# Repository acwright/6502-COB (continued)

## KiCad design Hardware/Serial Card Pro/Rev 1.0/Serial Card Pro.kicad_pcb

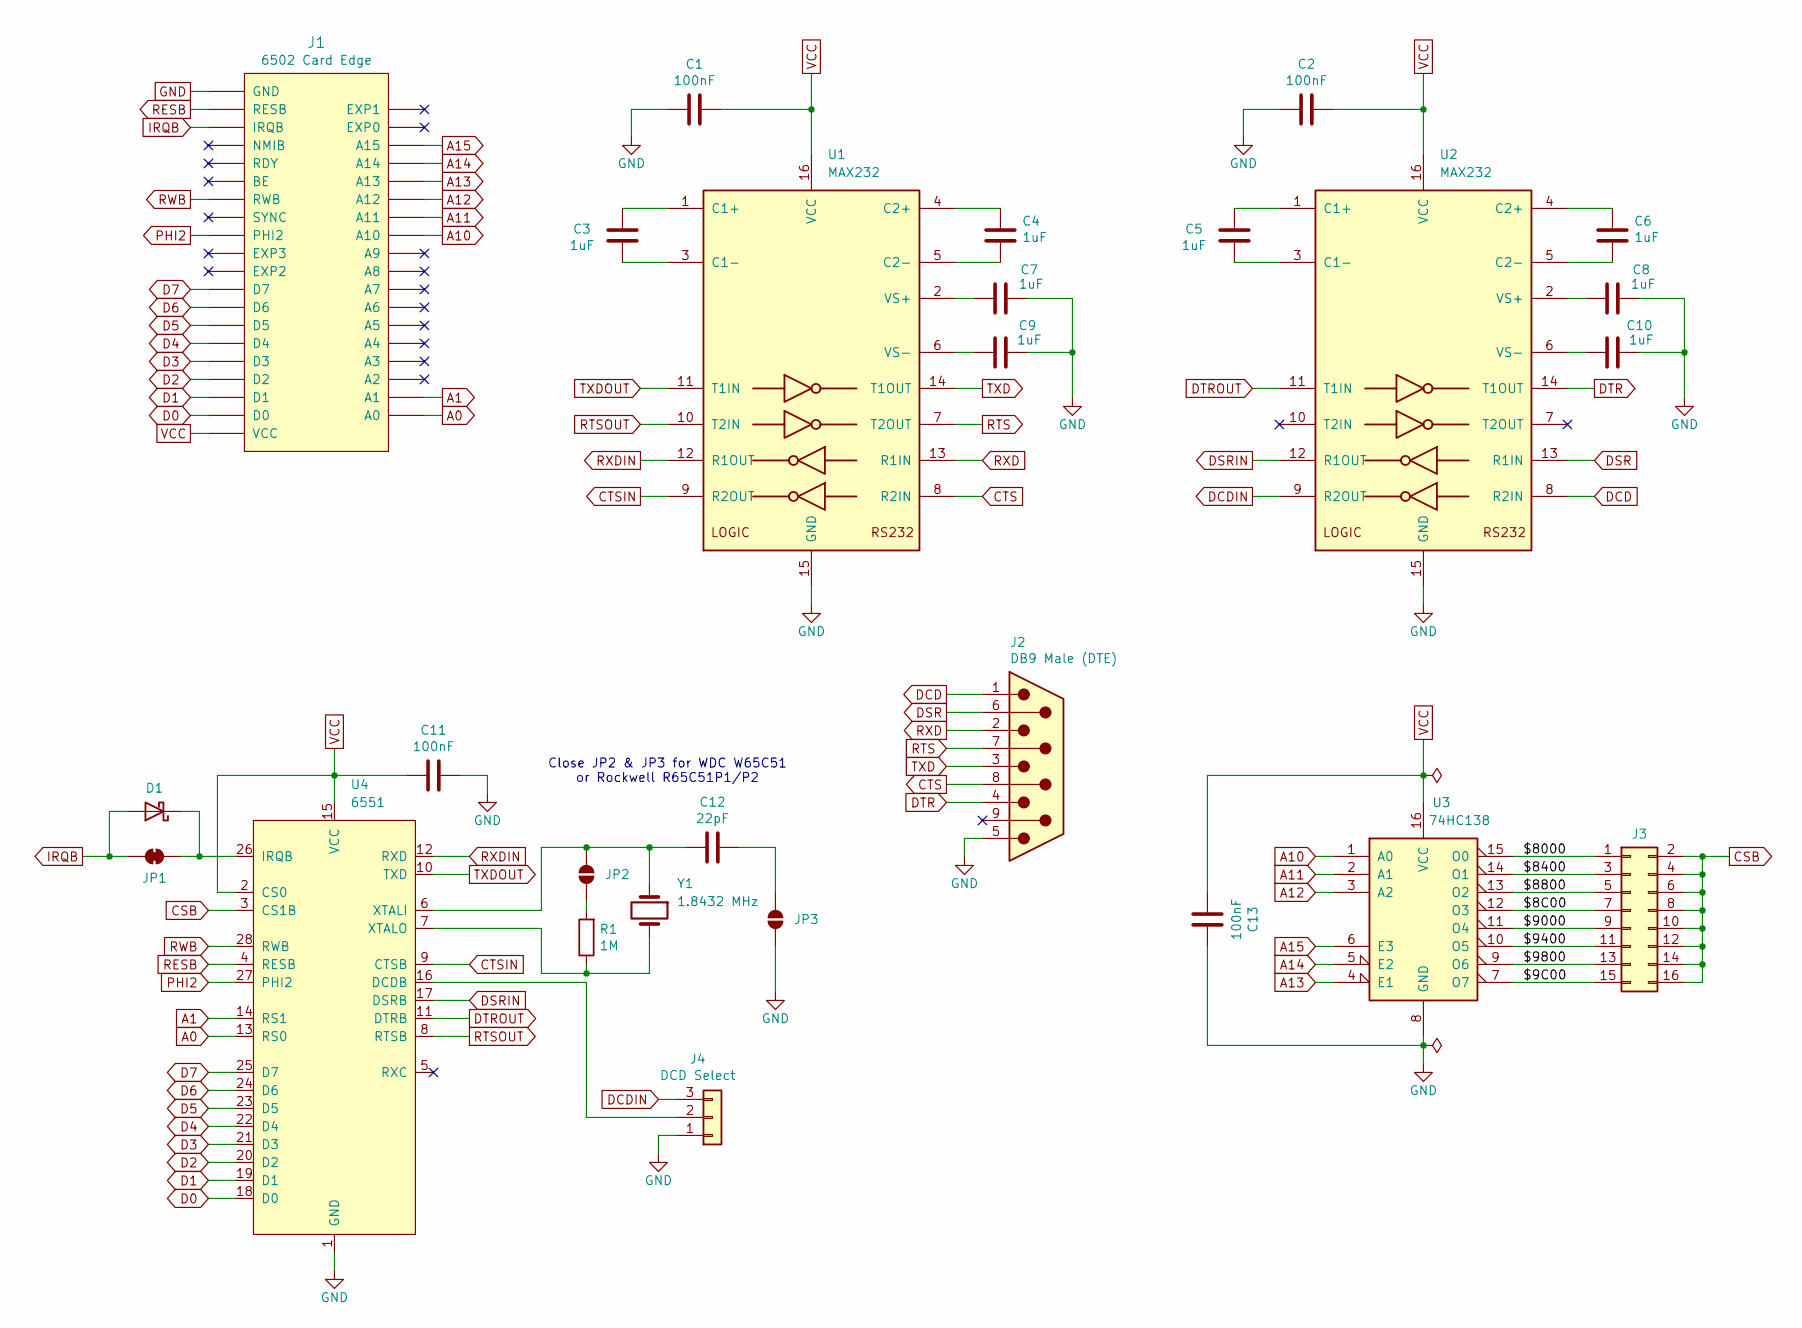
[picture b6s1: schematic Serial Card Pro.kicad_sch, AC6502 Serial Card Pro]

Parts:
C1, C2, C11, C13: 100nF; C_0805_2012Metric; LCSC C49678
C3, C4, C5, C6, C7, C8, C9, C10: 1uF; C_0805_2012Metric; LCSC C28323
C12: 22pF; C_0805_2012Metric; LCSC C1804
D1: BAT85; D_DO-35_SOD27_P7.62mm_Horizontal; Digikey BAT85SCT-ND
J1: 6502 Card Edge
J2: DB9 Male (DTE); DB9 Male; Digikey 609-1481-ND
J3: Conn_02x08_Odd_Even; PinHeader_2x08_P2.54mm_Vertical; Digikey S2011EC-40-ND
J4: DCD Select; PinHeader_1x03_P2.54mm_Vertical; Digikey S1011EC-40-ND
JP1: SolderJumper_2_Bridged; SolderJumper-2_P1.3mm_Bridged_RoundedPad1.0x1.5mm
JP2, JP3: SolderJumper_2_Open; SolderJumper-2_P1.3mm_Open_RoundedPad1.0x1.5mm
R1: 1M; R_0805_2012Metric; LCSC C17514
U1, U2: MAX232; SOIC-16; LCSC C59824
U3: 74HC138; SOIC-16_3.9x9.9mm_P1.27mm; LCSC C5602
U4: 6551; DIP-28_W15.24mm_Socket_LongPads
Y1: 1.8432 MHz; Crystal_HC49-U_Vertical; Digikey 535-9009-ND

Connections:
/$8C00: J3.7, U3.12 (O3)
/$9C00: J3.15, U3.7 (O7)
/$8000: J3.1, U3.15 (O0)
/$8400: J3.3, U3.14 (O1)
/$8800: J3.5, U3.13 (O2)
/$9000: J3.9, U3.11 (O4)
/$9400: J3.11, U3.10 (O5)
/$9800: J3.13, U3.9 (O6)
A0: J1.A0, U4.13 (RS0)
A1: J1.A1, U4.14 (RS1)
A10: J1.A10, U3.1 (A0)
A11: J1.A11, U3.2 (A1)
A12: J1.A12, U3.3 (A2)
A13: J1.A13, U3.4 (E1)
A14: J1.A14, U3.5 (E2)
A15: J1.A15, U3.6 (E3)
CSB: J3.2, J3.4, J3.6, J3.8, J3.10, J3.12, J3.14, J3.16, U4.3 (CS1B)
CTS: J2.8, U1.8 (R2IN)
CTSIN: U1.9 (R2OUT), U4.9 (CTSB)
D0: J1.D0, U4.18 (D0)
D1: J1.D1, U4.19 (D1)
D2: J1.D2, U4.20 (D2)
D3: J1.D3, U4.21 (D3)
D4: J1.D4, U4.22 (D4)
D5: J1.D5, U4.23 (D5)
D6: J1.D6, U4.24 (D6)
D7: J1.D7, U4.25 (D7)
DCD: J2.1, U2.8 (R2IN)
DCDIN: J4.3, U2.9 (R2OUT)
DSR: J2.6, U2.13 (R1IN)
DSRIN: U2.12 (R1OUT), U4.17 (DSRB)
DTR: J2.4, U2.14 (T1OUT)
DTROUT: U2.11 (T1IN), U4.11 (DTRB)
GND: C1.1, C2.1, C7.2, C8.2, C9.2, C10.2, C11.2, C13.2, J1.GND, J2.5, J4.1, JP3.1 (A), U1.15 (GND), U2.15 (GND), U3.8 (GND), U4.1 (GND)
IRQB: D1.2 (A), J1.IRQB, JP1.1 (A)
unnamed: D1.1 (K), JP1.2 (B), U4.26 (IRQB)
unnamed: J4.2, U4.16 (DCDB)
unnamed: JP2.1 (A), R1.2
unnamed: C12.2, JP2.2 (B), U4.6 (XTALI), Y1.1
unnamed: C12.1, JP3.2 (B)
unnamed: C3.1, U1.1 (C1+)
unnamed: C3.2, U1.3 (C1-)
unnamed: C4.1, U1.4 (C2+)
unnamed: C4.2, U1.5 (C2-)
unnamed: C7.1, U1.2 (VS+)
unnamed: C9.1, U1.6 (VS-)
unnamed: C5.1, U2.1 (C1+)
unnamed: C5.2, U2.3 (C1-)
unnamed: C6.1, U2.4 (C2+)
unnamed: C6.2, U2.5 (C2-)
unnamed: C8.1, U2.2 (VS+)
unnamed: C10.1, U2.6 (VS-)
unnamed: R1.1, U4.7 (XTALO), Y1.2
PHI2: J1.PHI2, U4.27 (PHI2)
RESB: J1.RESB, U4.4 (RESB)
RTS: J2.7, U1.7 (T2OUT)
RTSOUT: U1.10 (T2IN), U4.8 (RTSB)
RWB: J1.RWB, U4.28 (RWB)
RXD: J2.2, U1.13 (R1IN)
RXDIN: U1.12 (R1OUT), U4.12 (RXD)
TXD: J2.3, U1.14 (T1OUT)
TXDOUT: U1.11 (T1IN), U4.10 (TXD)
VCC: C1.2, C2.2, C11.1, C13.1, J1.VCC, U1.16 (VCC), U2.16 (VCC), U3.16 (VCC), U4.2 (CS0), U4.15 (VCC)

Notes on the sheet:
Close JP2 & JP3 for WDC W65C51 or Rockwell R65C51P1/P2

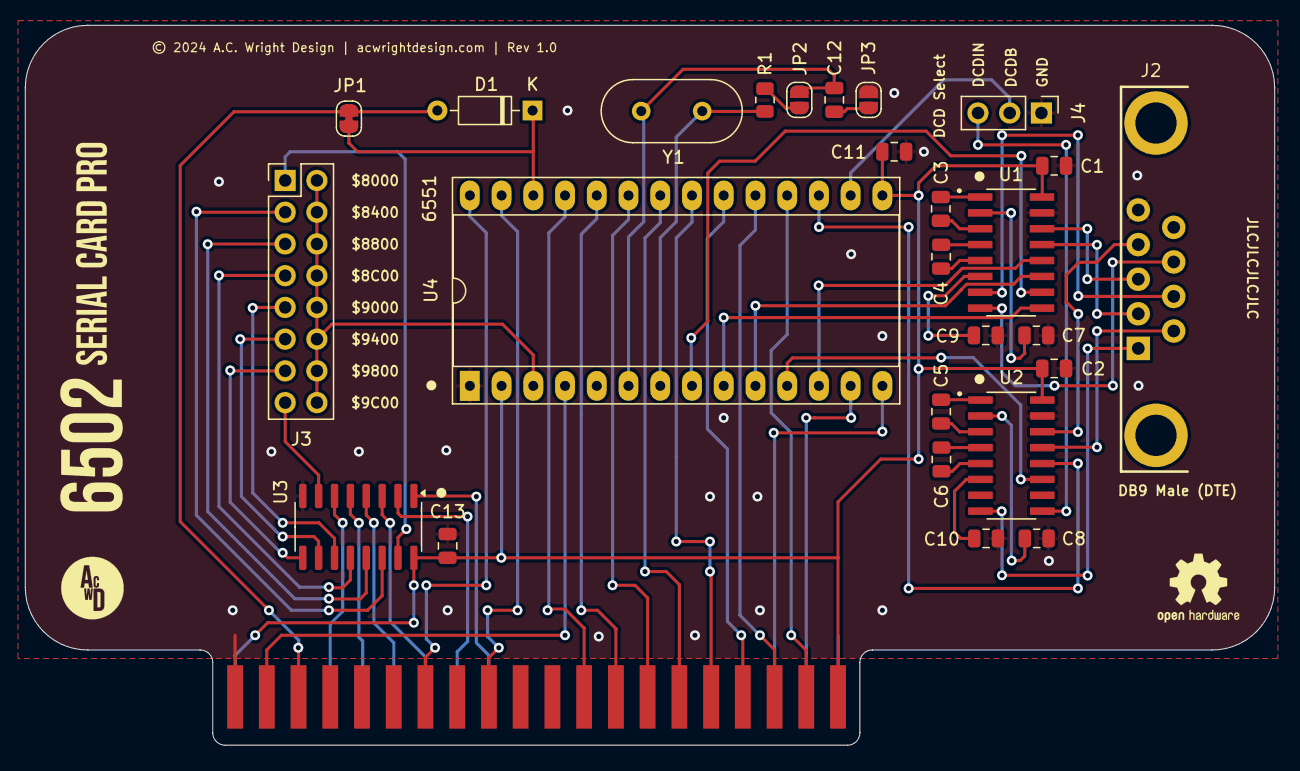
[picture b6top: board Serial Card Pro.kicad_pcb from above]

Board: 2 copper layers, 100.0 x 57.6 mm, 27 parts (0 on the bottom side), 63 nets.
